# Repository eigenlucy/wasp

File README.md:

# wasp

wearable ai assistant

Check out [the project page on my website](https://eigenlucy.github.io/projects/wasp/)

Created by lucy moglia <eigenlucy@proton.me>

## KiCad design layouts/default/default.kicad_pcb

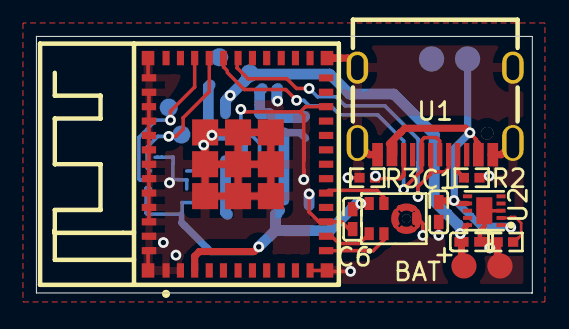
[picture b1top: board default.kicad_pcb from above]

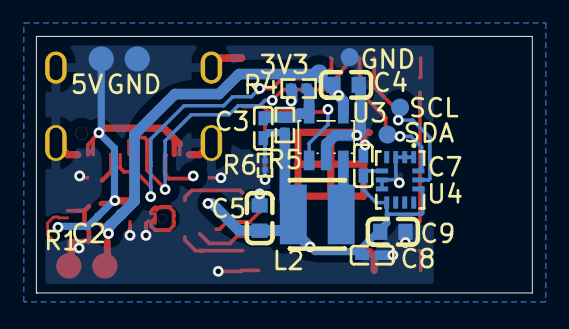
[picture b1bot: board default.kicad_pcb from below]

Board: 4 copper layers, 27.5 x 14.2 mm, 22 parts (12 on the bottom side), 17 nets.

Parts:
C1, C2: 1µF ±10% 16V X5R; C0402-b3ef17
C3, C6, C7, C8: 100nF ±10% 16V X7R; C0402-b3ef17
C4, C5, C9: 100nF ±10% 50V X7R; C0603-bd72f6
L1: WIRELM-SMD_AI-THINKER_PB-03-d07667
L2: IND-SMD_L3.0-W3.0-a13401
MIC1: MIC-SMD_5P-L3.5-W2.7-TL_MMICT390200012-12501e
R1: 560Ω ±1% 62.5mW; R0402-56259e
R2, R3: 5.1kΩ ±1% 62.5mW; R0402-56259e
R4: 200kΩ ±1% 62.5mW; R0402-56259e
R5: 953kΩ ±1% 62.5mW; R0402-56259e
R6: 10kΩ ±1% 50mW; R0201-27027e
U1: USB-C-SMD_KH-TYPE-C-16P
U2: WSON-10_L2.0-W2.0-P0.40-BL-EP
U3: SOT-23-5_L3.0-W1.7-P0.95-LS2.8-BR-9d80aa
U4: LGA-14_L3.0-W2.5-P0.50-TL-eab322

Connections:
B5: R3.1, U1.B5
CC1: R2.1, U1.A5
CLK: L1.16, MIC1.4
DATA: L1.13, MIC1.1
EN: L1.22, R6.1, U3.1
FB: C3.2, R4.1, R5.2, U3.5
ISET: R1.1, U2.2
SCL: L1.33, U4.13
SDA: L1.32, U4.14
SELECT: L1.12, MIC1.2
SW: L2.1, U3.3
gnd: C1.2, C2.2, C4.2, C5.2, C6.2, C7.2, C8.2, C9.2, L1.1, L1.2, L1.11, L1.14, L1.36, L1.37, L1.38, L1.39, L1.40, L1.41, L1.42, L1.43, L1.44, L1.45, L1.46, L1.47, L1.48, L1.49, L1.50, L1.51, L1.52, L1.53, L1.54, L1.55, L1.56, L1.57, L1.58, L1.59, L1.60, L1.61, MIC1.3, R1.2, R2.2, R3.2, R4.2, U1.1, U1.2, U1.3, U1.4, U1.A1, U1.A12, U1.B1, U1.B12, U2.3, U2.11, U3.2, U4.1, U4.2, U4.3, U4.6, U4.7
hv: C3.1, C5.1, C6.1, C7.1, C8.1, C9.1, L1.3, L2.2, MIC1.5, R5.1, R6.2, U4.5, U4.8, U4.12
hv-1: C1.1, U1.A4, U1.A9, U1.B4, U1.B9, U2.1, U2.7
hv-2: C2.1, C4.1, U2.10, U3.4
line: L1.30, U1.A7, U1.B7
line-1: L1.31, U1.A6, U1.B6

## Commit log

2025-05-19 finalish layout
2025-05-19 meow
2025-05-26 removed acc, fixed ldo (implement in main ncp release)
2025-05-26 almost done
2025-05-27 fixed workflow
2025-05-29 ready to order i think
